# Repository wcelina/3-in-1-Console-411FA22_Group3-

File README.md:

## 3-in-1 Console (Stopwatch, Counter, and Flappy Bird)
##### TLDR; On power up, the console should direct the user to the menu screen, where they can turn the knob to vary between the three modes and select the mode by clicking the rotary encoder. 

#
## Requirements:
##### Project management application - GanttProject 3.1.3
##### Circuit schematic design application - KiCad 6.0
##### Code software - Arduino IDE 2.0.3
##### 3D Design and Slicer - Tinkercad.com and Ultimaker Cura 5.2.1

#
## Recent Project Updates:

#### 12/8/22 - Presentation slides:
#### https://docs.google.com/presentation/d/1yn8I8TeqEF4ywxcgW0SFzS9HUh2eWH4x9auOoaWZxTw/edit?usp=sharing

#### 12/6/22 - All components and PCB are placed in a 3D printed compartment. Link of Flappy Bird demo:
#### https://drive.google.com/file/d/1Yfay8kJElGX3HygGRCzuhIqe8Dfigz_g/view?usp=sharing

#### 11/3/22 - The current breadboard prototype is wired with an LCD screen, push button, and power on/off switch. It successfully runs with a sample timer code. Due to complications and limitations of an LCD screen, we have placed an order for an OLED screen and will utilize that as soon as we receive it in about two business days (thank goodness for Amazon Prime). Link of demo below:
#### https://drive.google.com/drive/folders/1t0M0c-cClHCmyueLMgTcO8hawUu6y9SK

#
## Folder descriptions:

#### documents - Consists of weekly team documents and project information and specifications.

#### schematics - Consists of KiCad schematics and PCB layout, also available to view in PDF format.
##
### code:
##### rotarybutton - Testing program solely for the introduction of the rotary encoder and how it works
##### flappybird - Contains working Flappy Bird game
##### 411_combined_code - Contains menu option and selection from three modes: counter, stopwatch, and Flappy Bird

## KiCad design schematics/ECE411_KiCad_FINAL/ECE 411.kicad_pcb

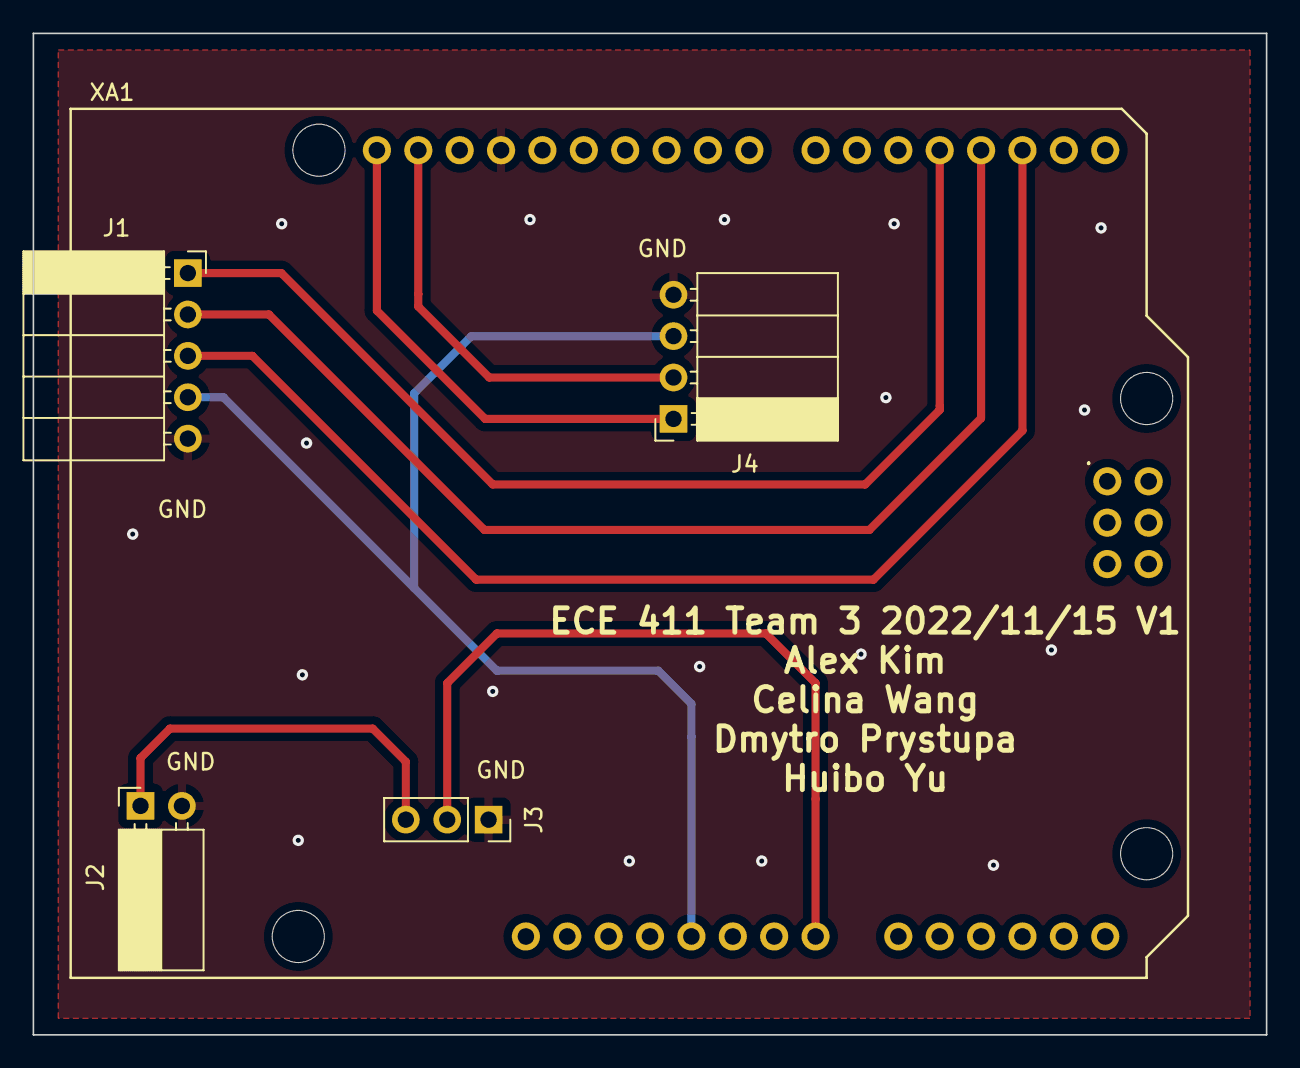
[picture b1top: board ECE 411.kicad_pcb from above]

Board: 2 copper layers, 75.7 x 61.5 mm, 5 parts (0 on the bottom side), 9 nets.

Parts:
J1: Rotary Encoder; PinSocket_1x05_P2.54mm_Horizontal
J2: Power; PinSocket_1x02_P2.54mm_Horizontal
J3: Switch; PinSocket_1x03_P2.54mm_Vertical
J4: LCD_I2C; PinSocket_1x04_P2.54mm_Horizontal
XA1: Arduino_Uno_Shield

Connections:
GND: J1.5, J2.2, J3.1, J4.4, XA1.GND1 (GND)
unnamed: J1.1, XA1.D4
unnamed: J1.2, XA1.D3 (D3_INT1)
unnamed: J1.3, XA1.D2 (D2_INT0)
unnamed: J1.4, J4.3, XA1.5V1 (5V)
unnamed: J2.1, J3.3
unnamed: J3.2, XA1.VIN
unnamed: J4.1, XA1.SCL
unnamed: J4.2, XA1.SDA

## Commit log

2022-10-12 "del"
2022-10-18 week 3 activity
2022-10-18 new folder
2022-10-20 Week 4 doc
2022-10-27 Week 5: Decision Matrix/AHP Methodology
2022-10-27 Week 5: Preliminary Schematic
2022-10-27 Week 5: Preliminary Schematic (updatedx1)
2022-11-03 Week 6: Gantt Chart
2022-11-03 Gantt Chart .gan file
2022-11-03 updated x1
2022-11-03 Full pdf file
2022-11-03 Week 6: Draft of KiCad schematic
2022-11-03 new folder for schematics
2022-11-03 kicad schematic file
2022-11-04 corrected gnd wire on right side
2022-11-04 corrected wire going to gnd on right side
2022-11-10 almost complete
2022-11-10 pdf version for quick viewing
2022-11-10 update extra line across power switch
2022-11-10 wk7: functional decomposition
2022-11-10 BOM excel and pdf
2022-11-15 updated pcb and circuit schematic
2022-11-15 quick view of PCD layout included
2022-11-17 final CAD
2022-12-01 week 10: test plans
2022-12-02 rotary encoder tester
2022-12-02 flappy bird game
2022-12-02 flappy bird code
2022-12-08 updated docs
2022-12-08 combined code along with menu
2022-12-08 fixed name typo
2022-12-10 add product photos
2022-12-10 added sketch
